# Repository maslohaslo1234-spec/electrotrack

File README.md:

# Electrotrack

Electrotrack is an experimental electromagnetic ball accelerator built around a custom ESP32-based PCB and a modular, 3D-printed circular track.

The electronics design and PCB layout are complete, and the mechanical CAD is in progress. The board has not been manufactured or tested. A first draft of the firmware (written with AI assistance) is included, but it has not been tested on hardware.

## Why I’m building it

I started this project after watching Hyperspace Pirate’s electromagnetic accelerator videos. I wanted to develop my own version and learn how to take a hardware project from a hand-drawn schematic to a custom PCB, mechanical design, firmware and a working prototype.

The project brings together several skills I want to improve: electronics design in KiCad, 3D modelling in Onshape, embedded programming and documenting the development process.

I am also reusing components I already have, including infrared sensors salvaged from a photocopier.

## What it is intended to do

The planned system will use infrared sensors to detect a steel ball moving around the track. An ESP32 will control four electromagnetic stages, and an OLED display is intended to show the measured ball speed.

The goal is to build and document a working experimental prototype, then compare the planned behaviour with the results of physical tests.

## Hardware overview

- **Controller:** ESP32 30-pin development board, plugged into the PCB.
- **Coil drivers:** Four channels using IRLZ44N N-channel MOSFETs, gate resistors, pull-down resistors and SB560 flyback diodes. Coils connect through screw terminals.
- **Position sensing:** Four IR sensor inputs on 3-pin JST XH connectors. The sensors were salvaged from a photocopier.
- **Power:** 3S LiPo input through an XT30 connector, with a fuse, on/off switch, bulk capacitor and L7805 regulator for the 5 V supply.
- **Display:** A 4-pin I2C header for a 0.96-inch OLED, intended to display ball speed.
- **Expansion:** A 1×10 header exposing spare ESP32 GPIO pins, 3.3 V and GND.
- **PCB:** A two-layer board designed in KiCad 10, with GND copper pours on both layers.

## ESP32 connections

The PCB uses an ESP32 30-pin DevKit. The numbers below are GPIO numbers, not physical connector-pin numbers.

### IR sensor inputs

| Connector | Receiver signal | Pull-up | ESP32 pin |
| --- | --- | --- | --- |
| J1 | OUT, connector pin 3 | R1 — 10 kΩ to 3.3 V | GPIO36 |
| J2 | OUT, connector pin 3 | R2 — 10 kΩ to 3.3 V | GPIO35 |
| J3 | OUT, connector pin 3 | R3 — 10 kΩ to 3.3 V | GPIO34 |
| J4 | OUT, connector pin 3 | R4 — 10 kΩ to 3.3 V | GPIO39 |

Each IR connector has the following pin assignment:

| Connector pin | Connection |
| --- | --- |
| 1 | IR emitter supply through a 150 Ω resistor (R5–R8) from 3.3 V |
| 2 | GND |
| 3 | Receiver output, connected to the corresponding ESP32 input |

GPIO34, GPIO35, GPIO36 and GPIO39 are input-only pins without internal pull-up resistors. The firmware therefore uses `INPUT`; the pull-ups are provided by the PCB.

### MOSFET gate connections

| MOSFET | ESP32 GPIO | Series gate resistor | Gate pull-down |
| --- | --- | --- | --- |
| Q1 | GPIO17 | R12 — 100 Ω | R15 — 10 kΩ to GND |
| Q2 | GPIO16 | R11 — 100 Ω | R13 — 10 kΩ to GND |
| Q3 | GPIO18 | R10 — 100 Ω | R14 — 10 kΩ to GND |
| Q4 | GPIO19 | R9 — 100 Ω | R16 — 10 kΩ to GND |

### OLED display

Connector J10 is intended for an I2C SSD1306 OLED.

| J10 pin | Signal | ESP32 connection |
| --- | --- | --- |
| 1 | SDA | GPIO21 |
| 2 | SCL | GPIO22 |
| 3 | Display supply | 3.3 V |
| 4 | Ground | GND |

### Expansion connector J11

| J11 pin | Connection |
| --- | --- |
| 1 | GND |
| 2 | 3.3 V |
| 3 | +5 V |
| 4 | GPIO5 |
| 5 | GPIO3 (RX0) |
| 6 | GPIO32 |
| 7 | GPIO33 |
| 8 | GPIO14 |
| 9 | GPIO13 |
| 10 | GPIO27 |

GPIO3 is the UART0 RX pin used for USB programming, and GPIO5 is a strapping pin, so avoid driving these externally during boot and flashing.

### Power connections

| ESP32 connection | PCB connection |
| --- | --- |
| VIN | Board's +5 V rail |
| 3.3 V | Logic supply for the sensor circuits and OLED |
| GND | Common PCB ground |

## Mechanical design

The mechanical parts are being designed in Onshape. The current CAD includes:

- Curved guide segments forming a circular track.
- Separate coil formers.
- IR sensor mounts.
- An initial assembly showing how the parts fit together.

The design is still in progress. No physical prints or fit tests have been completed yet, so the CAD assembly does not confirm real-world fit.

The mechanical part of the project is tracked separately:

[Electrotrack CAD repository](https://github.com/maslohaslo1234-spec/electrotrack-cad)

## Firmware

> **AI disclosure:** The firmware was written with AI assistance (vibe coding) and then reviewed and tidied up with AI tools. It is a first draft and has **not been tested on hardware**. Treat it as an untested starting point, not as verified code.

The sketch is in [`software/firmware/firmware.ino`](software/firmware/firmware.ino).

### How it works

One IR sensor is placed just before each of the four coils. When the ball is detected by sensor *i*:

1. Coil *i* is switched on to pull the ball in.
2. The firmware estimates when the ball will reach the centre of the coil, based on the speed measured between the two previous sensors.
3. Coil *i* is switched off at that moment, so the coil does not pull the ball back.

Ball speed is calculated as the sensor spacing divided by the time between two consecutive sensor events. The current speed, peak speed and hit count are shown on the OLED and printed to Serial.

The time-critical part is handled by a sensor interrupt (no floating-point maths, I2C or Serial inside it) and a high-priority sequencer task that busy-waits for the switch-off time with microsecond precision. The OLED runs in a separate low-priority task so it cannot delay switching.

### Controls

Press the on-board **BOOT** button to start or stop a run. At the start of a run, coil 0 is switched on to give the ball an initial pull, so the ball should rest just before sensor 0.

### Software safety features

- Each coil has a hard maximum on-time of 80 ms.
- When sensor *i* fires, coil *i − 1* is forced off, as a backstop for the timed switch-off.
- Only the expected sensor is accepted, which rejects noise and out-of-order events.
- A run is limited to 400 sensor events (about 100 laps).
- Any fault switches all coils off and latches a `FAULT` state until the next start.

These checks run in software only. A crash or freeze of the ESP32 while a coil is on is not covered, so the hardware limitations listed below still apply.

### Parameters to tune

| Constant | Meaning |
| --- | --- |
| `SENSOR_SPACING_MM` | Distance between two consecutive sensors along the track |
| `SENSOR_TO_CENTER_MM` | Distance from a sensor to the centre of its coil |
| `OFF_LEAD_US` | How early the coil is switched off, to compensate for acceleration and flyback decay |
| `FIRST_OFF_DELAY_US` | Switch-off delay for the first hit, when no speed is known yet |
| `COIL_MAX_ON_US` | Hard maximum on-time per coil activation |
| `IR_TRIGGER_EDGE` | `RISING` for the phototransistor sensors, `FALLING` for push-button simulation |

The geometry values are initial estimates and must be updated to match the final mechanical design. `OFF_LEAD_US` and `FIRST_OFF_DELAY_US` can only be tuned on the real hardware.

### Building

- Board: ESP32 Dev Module (ESP32 Arduino core).
- Libraries: Adafruit SSD1306 and Adafruit GFX.
- The pin mapping in the sketch matches the tables in [ESP32 connections](#esp32-connections).
- GPIO16 and GPIO17 drive MOSFET gates Q2 and Q1, so use a WROOM-based ESP32 board. WROVER modules use these pins for PSRAM.

### Known limitations

- Not tested on hardware, and the control logic is unverified.
- Timing parameters and geometry values are untuned.
- There is no hardware watchdog or independent coil cut-off.
- Failure modes such as a missed sensor event are handled only by the software timeout and fault state.

## Project files

| Path | Description |
| --- | --- |
| [`hardware/electrotrack.kicad_pro`](hardware/electrotrack.kicad_pro) | KiCad project file |
| [`hardware/electrotrack.kicad_sch`](hardware/electrotrack.kicad_sch) | Electronic schematic |
| [`hardware/electrotrack.kicad_pcb`](hardware/electrotrack.kicad_pcb) | PCB layout |
| [`hardware/electrotrack.pretty/`](hardware/electrotrack.pretty/) | Custom footprint library, including the ESP32 30-pin footprint |
| [`hardware/electrotrack.csv`](hardware/electrotrack.csv) | Electronic component list exported from KiCad |
| [`software/firmware/firmware.ino`](software/firmware/firmware.ino) | ESP32 firmware (AI-assisted first draft, untested) |
| [`gerber/`](gerber/) | PCB fabrication Gerber exports |
| [`drill files/`](drill%20files/) | PCB drill exports |
| [`pdf/`](pdf/) | PDF plots of the PCB layers |
| [`BOM.md`](BOM.md) | Half Life funding and purchasing tracker |
| [`JOURNAL.md`](JOURNAL.md) | Development journal mirrored from Half Life |

To inspect the electronics design, open `hardware/electrotrack.kicad_pro` in KiCad 10. Keep the custom footprint library and library configuration files alongside the project.

## Status

- [x] Concept and hand-drawn schematic
- [x] KiCad schematic and component-list export
- [x] Two-layer PCB layout
- [x] PCB design rule check completed with 0 errors
- [x] Gerber and drill fabrication exports
- [x] Initial track, coil bobbin and IR sensor mount models
- [x] Initial mechanical assembly in Onshape
- [x] First firmware draft (AI-assisted, untested)
- [ ] Finish mechanical design and check fit
- [ ] Order PCB and parts
- [ ] Assemble and test the board
- [ ] Manufacture and assemble the mechanical parts
- [ ] Test and tune the firmware on hardware
- [ ] Implement and verify speed measurement
- [ ] Test the complete system

## Design notes and known limitations

This is an unverified first revision.

- **MOSFET control:** Compatibility between the ESP32 outputs and the selected MOSFETs still requires verification.
- **Power and thermal behaviour:** Current consumption, protection and regulator temperatures have not been physically tested.
- **Firmware:** An AI-assisted first draft exists but has not been tested on hardware; the control logic, timing parameters and fault handling remain to be verified.
- **Polarity protection:** The PCB does not include dedicated reverse-polarity protection.
- **Mechanical fit:** Clearances, printed-part fit and assembly access have not been verified with physical parts.
- **Measurements:** No ball-speed measurements or complete-system test results are available yet.

## Documentation

I am making an effort to document this project in English, but my English is still limited. I use AI tools to help translate and improve the English in my project documentation.

The firmware was also written with AI assistance (vibe coding); see the [Firmware](#firmware) section.

The funding BOM and development journal are synchronized from [Half Life](https://halflife.hackclub.com/).

## Safety

This is an experimental project involving high currents, stored electrical energy and a moving steel ball. The design has not been manufactured or validated, and this repository should not be treated as a tested construction guide.

## License

See [`LICENSE`](LICENSE).

## Inspiration

Inspired by Hyperspace Pirate’s electromagnetic accelerator project.

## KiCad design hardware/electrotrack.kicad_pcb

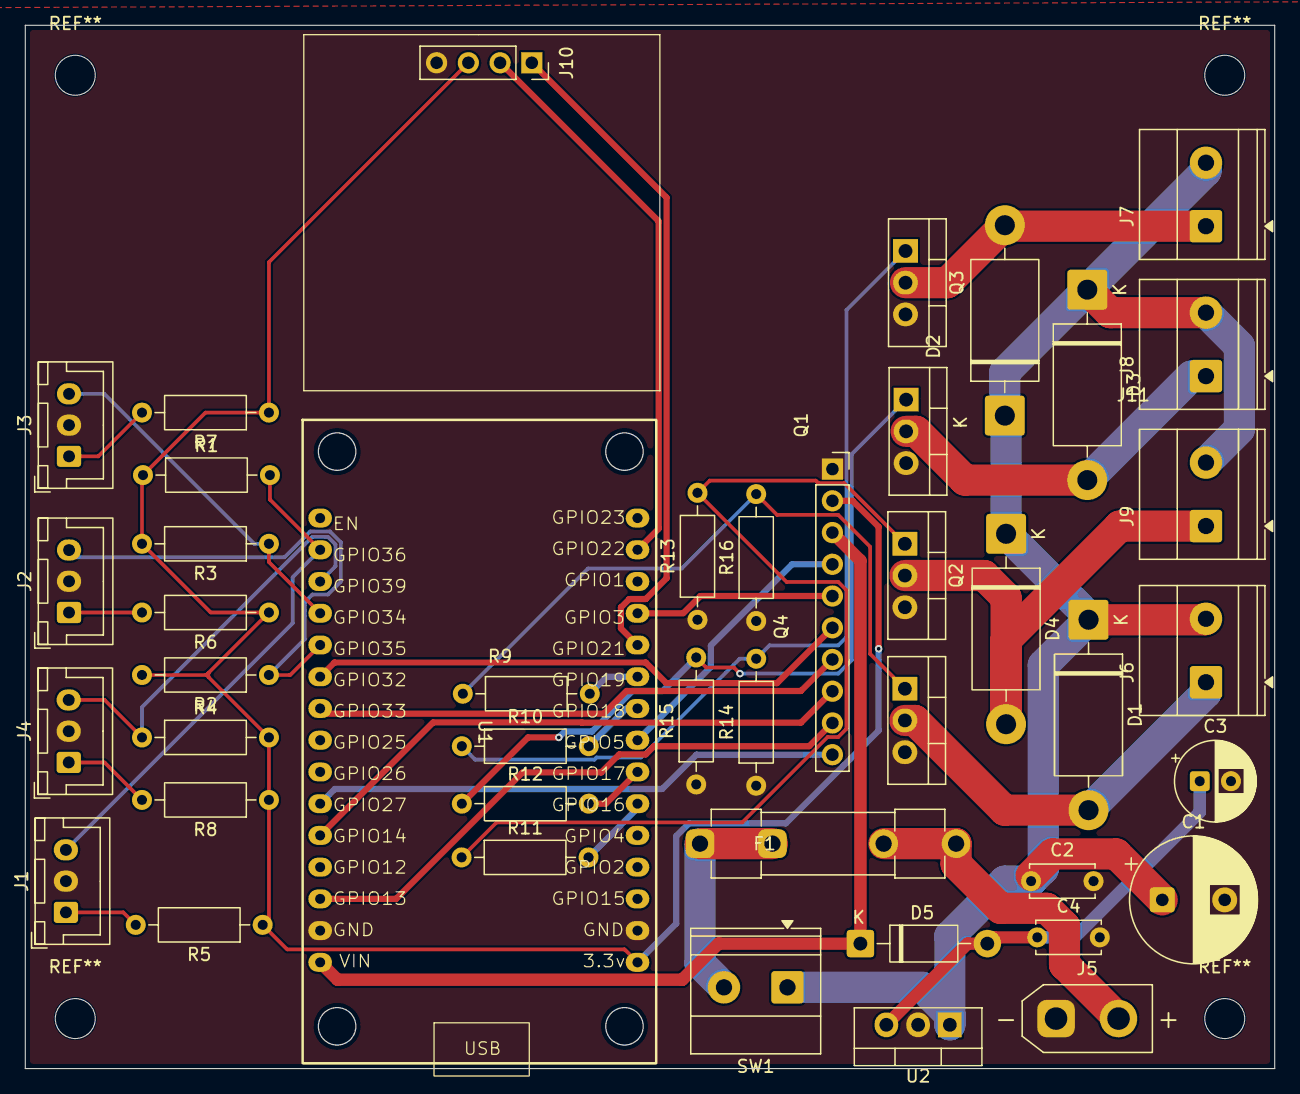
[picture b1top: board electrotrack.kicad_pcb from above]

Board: 2 copper layers, 100.0 x 83.5 mm, 44 parts (0 on the bottom side), 36 nets.

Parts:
C1: electrolitic 1000μF; CP_Radial_D10.0mm_P5.00mm
C2: C 100nF; C_Disc_D5.0mm_W2.5mm_P5.00mm
C3: 100 µF; CP_Radial_D6.3mm_P2.50mm
C4: 100nF; C_Disc_D5.0mm_W2.5mm_P5.00mm
D1, D2, D3, D4: SB560; D_DO-201AD_P15.24mm_Horizontal
D5: 1N5819; D_DO-41_SOD81_P10.16mm_Horizontal
F1: 5A fast; Fuseholder_Clip-5x20mm_Littelfuse_520_Inline_P20.50x5.80mm_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
J1, J2, J3, J4: IR; JST_XH_B3B-XH-A_1x03_P2.50mm_Vertical
J5: XT30; AMASS_XT30UPB-M_1x02_P5.0mm_Vertical
J6, J7, J8, J9: Coil; TerminalBlock_Phoenix_MKDS-1,5-2-5.08_1x02_P5.08mm_Horizont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
J10: 0.96 inch OLED; PinSocket_1x04_P2.54mm_Vertical
J11: Conn_01x10_Pin; PinSocket_1x10_P2.54mm_Vertical
Q1, Q2, Q3, Q4: IRLZ44N; TO-220-3_Vertical
R1, R2, R3, R4: 10k Ω; R_Axial_DIN0207_L6.3mm_D2.5mm_P10.16mm_Horizontal
R5, R6, R7, R8: 150Ω; R_Axial_DIN0207_L6.3mm_D2.5mm_P10.16mm_Horizontal
R9, R10, R11, R12: 100Ω; R_Axial_DIN0207_L6.3mm_D2.5mm_P10.16mm_Horizontal
R13, R14, R15, R16: 10kΩ; R_Axial_DIN0207_L6.3mm_D2.5mm_P10.16mm_Horizontal
SW1: SW_SPST; TerminalBlock_Phoenix_MKDS-1,5-2-5.08_1x02_P5.08mm_Horizont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
U1: ESP32_30pin
U2: L7805; TO-220-3_Vertical

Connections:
+3.3V: J10.3, J11.2, R1.1, R2.2, R3.2, R4.2, R5.1, R6.1, R7.1, R8.1, U1.16 (3.3v)
+5V: D5.1 (K), J11.3, U1.1 (VIN)
+12V: C1.1, C2.1, D1.1 (K), D2.1 (K), D3.1 (K), D4.1 (K), J6.2, J7.2, J8.2, J9.2, SW1.1 (A), U2.1 (IN)
GND: C1.2, C2.2, C3.2, C4.2, J1.2, J2.2, J3.2, J4.2, J5.1, J10.4, J11.1, Q1.3 (S), Q2.3 (S), Q3.3 (S), Q4.3 (S), R13.1, R14.1, R15.1, R16.1, U1.2 (GND), U1.17 (GND), U2.2 (GND)
unnamed: D1.2 (A), J6.1, Q4.2 (D)
unnamed: D2.2 (A), J7.1, Q3.2 (D)
unnamed: D3.2 (A), J8.1, Q1.2 (D)
unnamed: D4.2 (A), J9.1, Q2.2 (D)
unnamed: C3.1, C4.1, D5.2 (A), U2.3 (OUT)
unnamed: J1.1, R5.2
unnamed: J1.3, R1.2, U1.14 (GPIO36)
unnamed: J2.1, R6.2
unnamed: J2.3, R2.1, U1.11 (GPIO35)
unnamed: J3.1, R7.2
unnamed: J3.3, R3.1, U1.12 (GPIO34)
unnamed: J4.1, R8.2
unnamed: J4.3, R4.1, U1.13 (GPIO39)
unnamed: F1.2, J5.2
unnamed: J10.1, U1.26 (GPIO21)
unnamed: J10.2, U1.29 (GPIO22)
unnamed: J11.4, U1.23 (GPIO5)
unnamed: J11.5, U1.27 (GPIO3)
unnamed: J11.6, U1.10 (GPIO32)
unnamed: J11.7, U1.9 (GPIO33)
unnamed: J11.8, U1.5 (GPIO14)
unnamed: J11.9, U1.3 (GPIO13)
unnamed: J11.10, U1.6 (GPIO27)
unnamed: Q1.1 (G), R12.1, R15.2
unnamed: Q2.1 (G), R11.1, R13.2
unnamed: Q3.1 (G), R10.1, R14.2
unnamed: Q4.1 (G), R9.1, R16.2
unnamed: F1.1, SW1.2 (B)
unnamed: R11.2, U1.21 (GPIO16)
unnamed: R12.2, U1.22 (GPIO17)
unnamed: R10.2, U1.24 (GPIO18)
unnamed: R9.2, U1.25 (GPIO19)
